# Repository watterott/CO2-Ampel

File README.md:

# CO2-Ampel
The CO2-Ampel is a traffic light to show the carbon dioxide concentration in a room.

* [Microchip ATSAMD21](https://www.microchip.com/wwwproducts/en/ATSAMD21G18) ARM Cortex-M0+ Microcontroller
* Sensirion [SCD30](https://www.sensirion.com/en/environmental-sensors/carbon-dioxide-sensors/carbon-dioxide-sensors-scd30/) or [SCD40/SCD41](https://www.sensirion.com/en/environmental-sensors/carbon-dioxide-sensors/carbon-dioxide-sensor-scd4x/) CO2 Sensor
* Intelligent WS2812 RGB-LEDs
* Acoustic Buzzer
* Plus Version:
  * [Microchip ATWINC1500B](http://www.microchip.com/wwwproducts/en/ATWINC1500) WiFi/WLAN Network Controller
* Pro Version:
  * Air Pressure Sensor
  * [Microchip ATWINC1500B](http://www.microchip.com/wwwproducts/en/ATWINC1500) WiFi/WLAN Network Controller (optional)
  * [HopeRF RFM95W/RFM96W](https://www.hoperf.com/modules/lora/index.html) LoRa Transceiver (optional)
* USB-C connector for power and data/programming
* USB CDC+MSC Bootloader (Arduino compatible)
* Open-Source and released under the [Creative Commons Attribution Share-Alike License](https://creativecommons.org/licenses/by-sa/4.0/).
* **[Documentation on learn.watterott.com](https://learn.watterott.com/breakouts/co2-ampel/)**

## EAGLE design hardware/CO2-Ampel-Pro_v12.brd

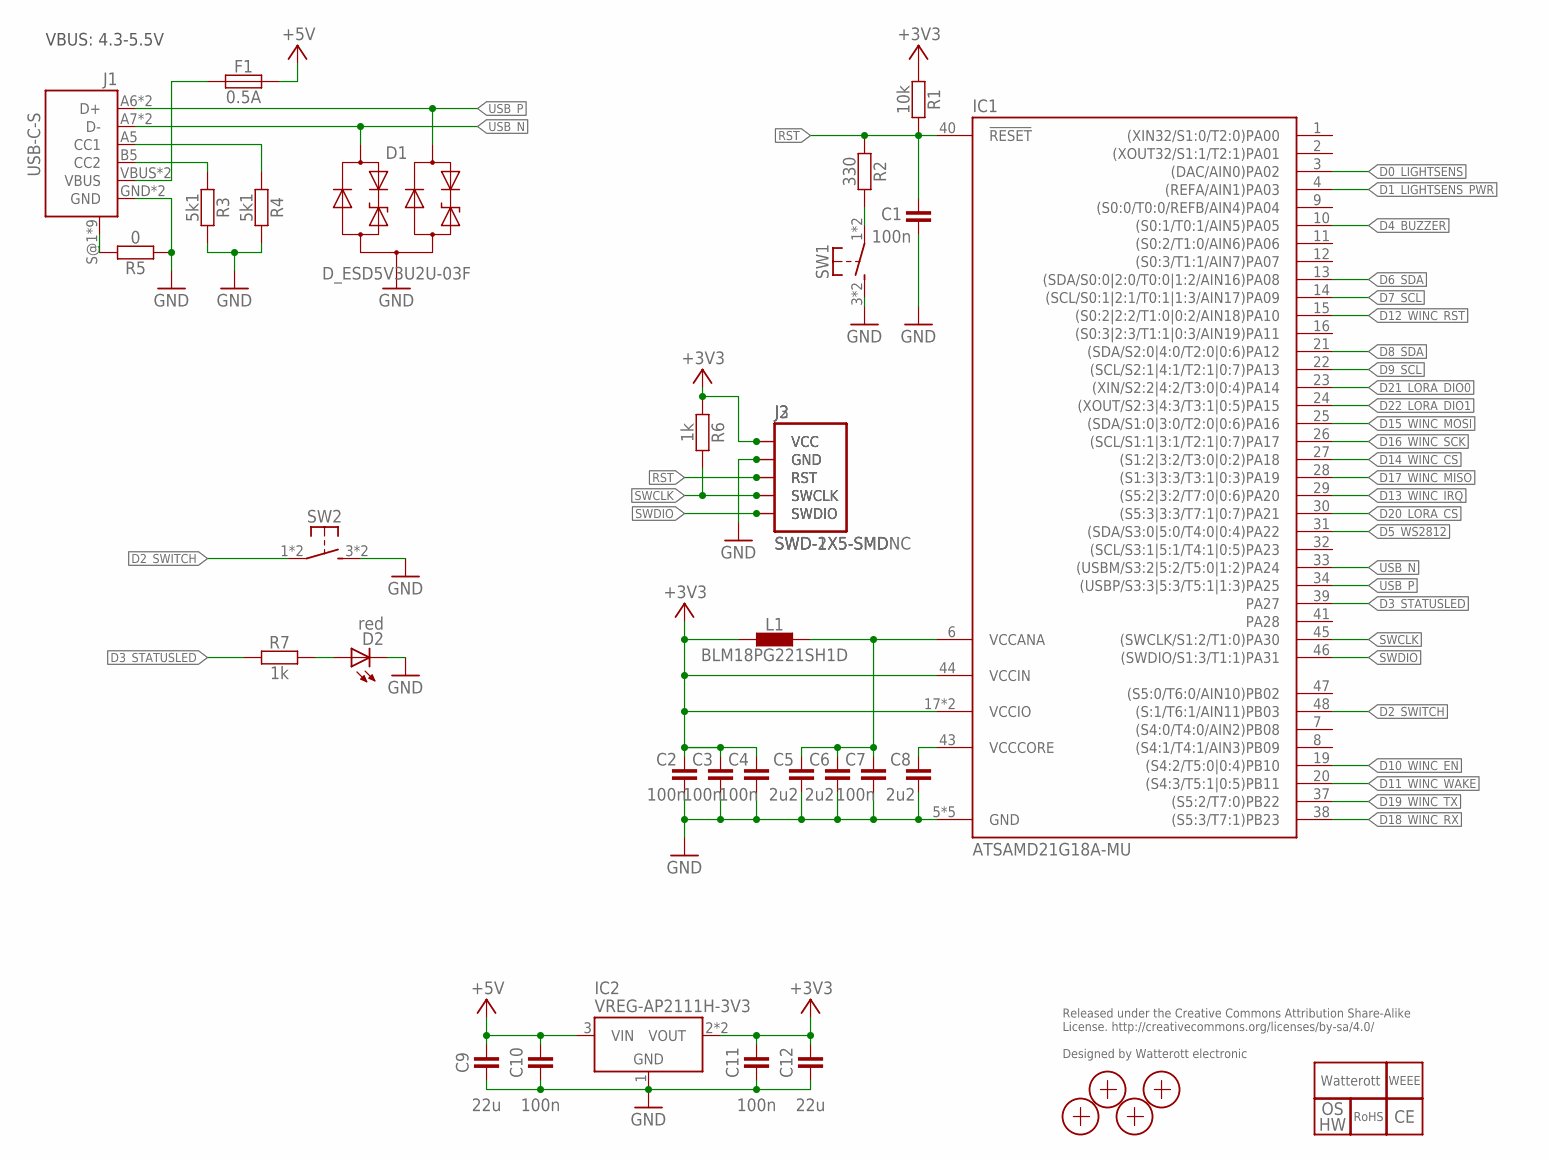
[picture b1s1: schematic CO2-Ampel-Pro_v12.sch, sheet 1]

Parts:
C1, C2, C3, C4, C7, C10, C11: 100n; C0402
C5, C6, C8: 2u2; C0402
C9, C12: 22u; C0805
D1: D_ESD5V3U2U-03F; SOT723
D2: red; C0603
F1: 0.5A; C0805
IC1: ATSAMD21G18A-MU; QFN48-PAD
IC2: VREG-AP2111H-3V3; SOT223
J1: USB-C-S
J2: SWD-2X5-SMD; SWD-2X5_SMD
J3: SWD-1X5-SMDNC; SWD-1X5_SMDNC
L1: BLM18PG221SH1D; C0603
LOGO1: LOGO_SPARK-4; SPARK_4MM
LOGO2: LOGO_WEEE-4; WEEE_4MM
LOGO3: OSHW_LOGOX0070; OSHW_3MM
LOGO4: LOGO_ROHS-4; ROHS_4MM
LOGO5: LOGO_CE-4; CE_4MM
R1: 10k; C0402
R2: 330; C0402
R3, R4: 5k1; C0402
R5: 0; C0603
R6, R7: 1k; C0402
SW1: PTS645SK50SMTR92-Red; PTS840P
SW2: PTS645SH50SMTR92-Grey; PTS840P
X1, X2, X3, X4: PASSER-07; PASSER_07MM

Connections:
+3V3: C2.2, C3.2, C4.2, C11.2, C12.2, IC1.17 (VCCIO), IC1.36 (VCCIO), IC1.44 (VCCIN), IC2.2 (VOUT), IC2.4 (VOUT), J2.VCC, J3.1-VCC (VCC), L1.1, R1.1, R6.1; also elsewhere on the board
+5V: C9.2, C10.2, F1.2, IC2.3 (VIN); also elsewhere on the board
CC1: J1.A5 (CC1), R4.1
CC2: J1.B5 (CC2), R3.1
D0_LIGHTSENS: IC1.3 ((DAC/AIN0)PA02); also elsewhere on the board
D1_LIGHTSENS_PWR: IC1.4 ((REFA/AIN1)PA03); also elsewhere on the board
D2_SWITCH: IC1.48 ((S:1/T6:1/AIN11)PB03), SW2.1, SW2.2 (P1)
D3_STATUSLED: IC1.39 (PA27), R7.1
D4_BUZZER: IC1.10 ((S0:1/T0:1/AIN5)PA05); also elsewhere on the board
D5_WS2812: IC1.31 ((SDA/S3:0|5:0/T4:0|0:4)PA22); also elsewhere on the board
D6_SDA: IC1.13 ((SDA/S0:0|2:0/T0:0|1:2/AIN16)PA08); also elsewhere on the board
D7_SCL: IC1.14 ((SCL/S0:1|2:1/T0:1|1:3/AIN17)PA09); also elsewhere on the board
D8_SDA: IC1.21 ((SDA/S2:0|4:0/T2:0|0:6)PA12); also elsewhere on the board
D9_SCL: IC1.22 ((SCL/S2:1|4:1/T2:1|0:7)PA13); also elsewhere on the board
D10_WINC_EN: IC1.19 ((S4:2/T5:0|0:4)PB10); also elsewhere on the board
D11_WINC_WAKE: IC1.20 ((S4:3/T5:1|0:5)PB11); also elsewhere on the board
D12_WINC_RST: IC1.15 ((S0:2|2:2/T1:0|0:2/AIN18)PA10); also elsewhere on the board
D13_WINC_IRQ: IC1.29 ((S5:2|3:2/T7:0|0:6)PA20); also elsewhere on the board
D14_WINC_CS: IC1.27 ((S1:2|3:2/T3:0|0:2)PA18); also elsewhere on the board
D15_WINC_MOSI: IC1.25 ((SDA/S1:0|3:0/T2:0|0:6)PA16); also elsewhere on the board
D16_WINC_SCK: IC1.26 ((SCL/S1:1|3:1/T2:1|0:7)PA17); also elsewhere on the board
D17_WINC_MISO: IC1.28 ((S1:3|3:3/T3:1|0:3)PA19); also elsewhere on the board
D18_WINC_RX: IC1.38 ((S5:3/T7:1)PB23); also elsewhere on the board
D19_WINC_TX: IC1.37 ((S5:2/T7:0)PB22); also elsewhere on the board
D20_LORA_CS: IC1.30 ((S5:3|3:3/T7:1|0:7)PA21); also elsewhere on the board
D21_LORA_DIO0: IC1.23 ((XIN/S2:2|4:2/T3:0|0:4)PA14); also elsewhere on the board
D22_LORA_DIO1: IC1.24 ((XOUT/S2:3|4:3/T3:1|0:5)PA15); also elsewhere on the board
GND: C1.1, C2.1, C3.1, C4.1, C5.1, C6.1, C7.1, C8.1, C9.1, C10.1, C11.1, C12.1, D1.3 (A), D2.C, IC1.5 (GND), IC1.18 (GND), IC1.35 (GND), IC1.42 (GND), IC1.TP (GND), IC2.1 (GND), J1.GND, J1.GND2 (GND), J2.GND@1 (GND), J2.GND@2 (GND), J2.GND@3 (GND), J3.2-GND (GND), R3.2, R4.2, R5.1, SW1.3 (S1), SW1.4 (S1), SW2.3 (S1), SW2.4 (S1); also elsewhere on the board
unnamed: D2.A, R7.2
unnamed: R2.2, SW1.1, SW1.2 (P1)
RST: C1.2, IC1.40 (!RESET), J2.RST, J3.3-RST (RST), R1.2, R2.1
SHLD: J1.S@1 (SHIELD), J1.S@2 (SHIELD), J1.S@3 (SHIELD), J1.S@4 (SHIELD), J1.S@5 (SHIELD), J1.S@6 (SHIELD), J1.S@7 (SHIELD), J1.S@8 (SHIELD), J1.S@9 (SHIELD), R5.2
SWCLK: IC1.45 ((SWCLK/S1:2/T1:0)PA30), J2.SWCLK, J3.4-SWDCLK (SWCLK), R6.2
SWDIO: IC1.46 ((SWDIO/S1:3/T1:1)PA31), J2.SWDIO, J3.5-SWDIO (SWDIO)
USB_N: D1.1 (C1), IC1.33 ((USBM/S3:2|5:2/T5:0|1:2)PA24), J1.A7 (D-), J1.B7 (D-)
USB_P: D1.2 (C2), IC1.34 ((USBP/S3:3|5:3/T5:1|1:3)PA25), J1.A6 (D+), J1.B6 (D+)
VBUS: F1.1, J1.VBUS, J1.VBUS2 (VBUS)
VCCANA: C5.2, C6.2, C7.2, IC1.6 (VCCANA), L1.2
VCCCORE: C8.2, IC1.43 (VCCCORE)

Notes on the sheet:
Released under the Creative Commons Attribution Share-Alike License. http://creativecommons.org/licenses/by-sa/4.0/ Designed by Watterott electronic
VBUS: 4.3-5.5V

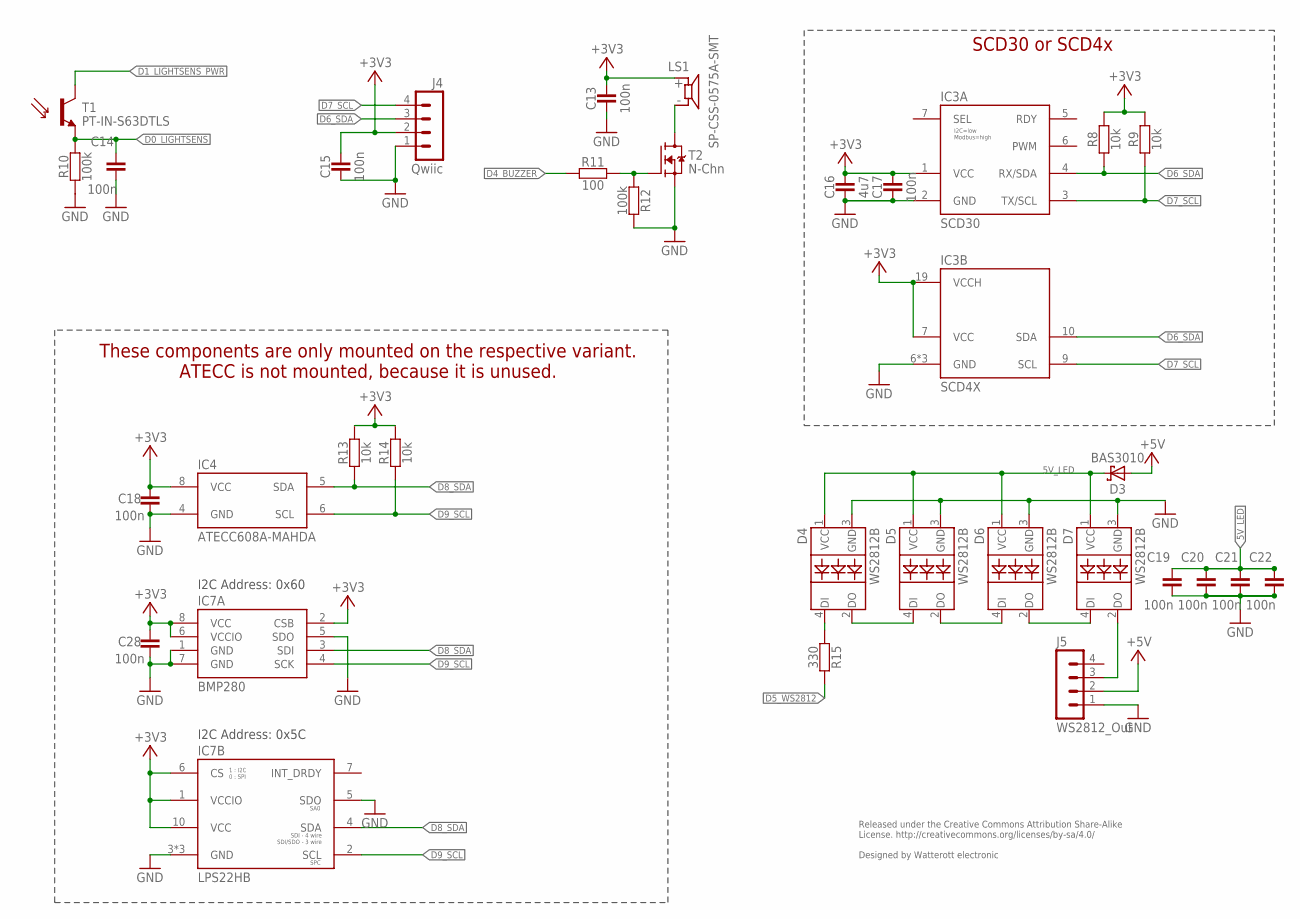
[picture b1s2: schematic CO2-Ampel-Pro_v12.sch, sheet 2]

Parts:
C13, C14, C15, C17, C18, C19, C20, C21, C22, C28: 100n; C0402
C16: 4u7; C0402
D3: BAS3010; SOD323
D4, D5, D6, D7: WS2812B
IC3A: SCD30
IC3B: SCD4X
IC4: ATECC608A-MAHDA; UDFN8
IC7A: BMP280; LGA8
IC7B: LPS22HB
J4: Qwiic; JST_SM04B-SRSS-TB
J5: WS2812_Out; JST_SM04B-SRSS-TB
LS1: SP-CSS-0575A-SMT; CUI_CSS-0575A-SMT
R8, R9, R13, R14: 10k; C0402
R10, R12: 100k; C0402
R11: 100; C0402
R15: 330; C0402
T1: PT-IN-S63DTLS; C0603T
T2: N-Chn; SOT23

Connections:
5V_LED: C19.2, C20.2, C21.2, C22.2, D3.C, D4.1 (VCC), D5.1 (VCC), D6.1 (VCC), D7.1 (VCC)
+3V3: C13.2, C15.2, C16.2, C17.2, C18.2, C28.2, IC3A.1 (VCC), IC3B.7 (VCC), IC3B.19 (VCCH), IC4.8 (VCC), IC7A.2 (CSB), IC7A.6 (VCCIO), IC7A.8 (VCC), IC7B.1 (VCCIO), IC7B.6 (CS), IC7B.10 (VCC), J4.2, LS1.+, R8.2, R9.2, R13.2, R14.2; also elsewhere on the board
+5V: D3.A, J5.2; also elsewhere on the board
D0_LIGHTSENS: C14.2, R10.2, T1.E; also elsewhere on the board
D1_LIGHTSENS_PWR: T1.C; also elsewhere on the board
D4_BUZZER: R11.1; also elsewhere on the board
D5_WS2812: R15.2; also elsewhere on the board
D6_SDA: IC3A.4 (RX/SDA), IC3B.10 (SDA), J4.3, R8.1; also elsewhere on the board
D7_SCL: IC3A.3 (TX/SCL), IC3B.9 (SCL), J4.4, R9.1; also elsewhere on the board
D8_SDA: IC4.5 (SDA), IC7A.3 (SDI), IC7B.4 (SDA), R13.1; also elsewhere on the board
D9_SCL: IC4.6 (SCL), IC7A.4 (SCK), IC7B.2 (SCL), R14.1; also elsewhere on the board
GND: C13.1, C14.1, C15.1, C16.1, C17.1, C18.1, C19.1, C20.1, C21.1, C22.1, C28.1, D4.3 (GND), D5.3 (GND), D6.3 (GND), D7.3 (GND), IC3A.2 (GND), IC3B.6 (GND), IC3B.20 (GND), IC3B.21 (GND), IC4.4 (GND), IC7A.1 (GND), IC7A.5 (SDO), IC7A.7 (GND), IC7B.3 (GND), IC7B.5 (SDO), IC7B.8 (GND), IC7B.9 (GND), J4.1, J5.1, R10.1, R12.2, T2.2 (S); also elsewhere on the board
unnamed: LS1.- (N), T2.3 (D)
unnamed: R11.2, R12.1, T2.1 (G)
W1IN: D4.4 (DI), R15.1
W1OUT: D4.2 (DO), D5.4 (DI)
W2OUT: D5.2 (DO), D6.4 (DI)
W3OUT: D6.2 (DO), D7.4 (DI)
W4OUT: D7.2 (DO), J5.3

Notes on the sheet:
I2C Address: 0x60
Released under the Creative Commons Attribution Share-Alike License. http://creativecommons.org/licenses/by-sa/4.0/ Designed by Watterott electronic
I2C Address: 0x5C
These components are only mounted on the respective variant. ATECC is not mounted, because it is unused.
SCD30 or SCD4x

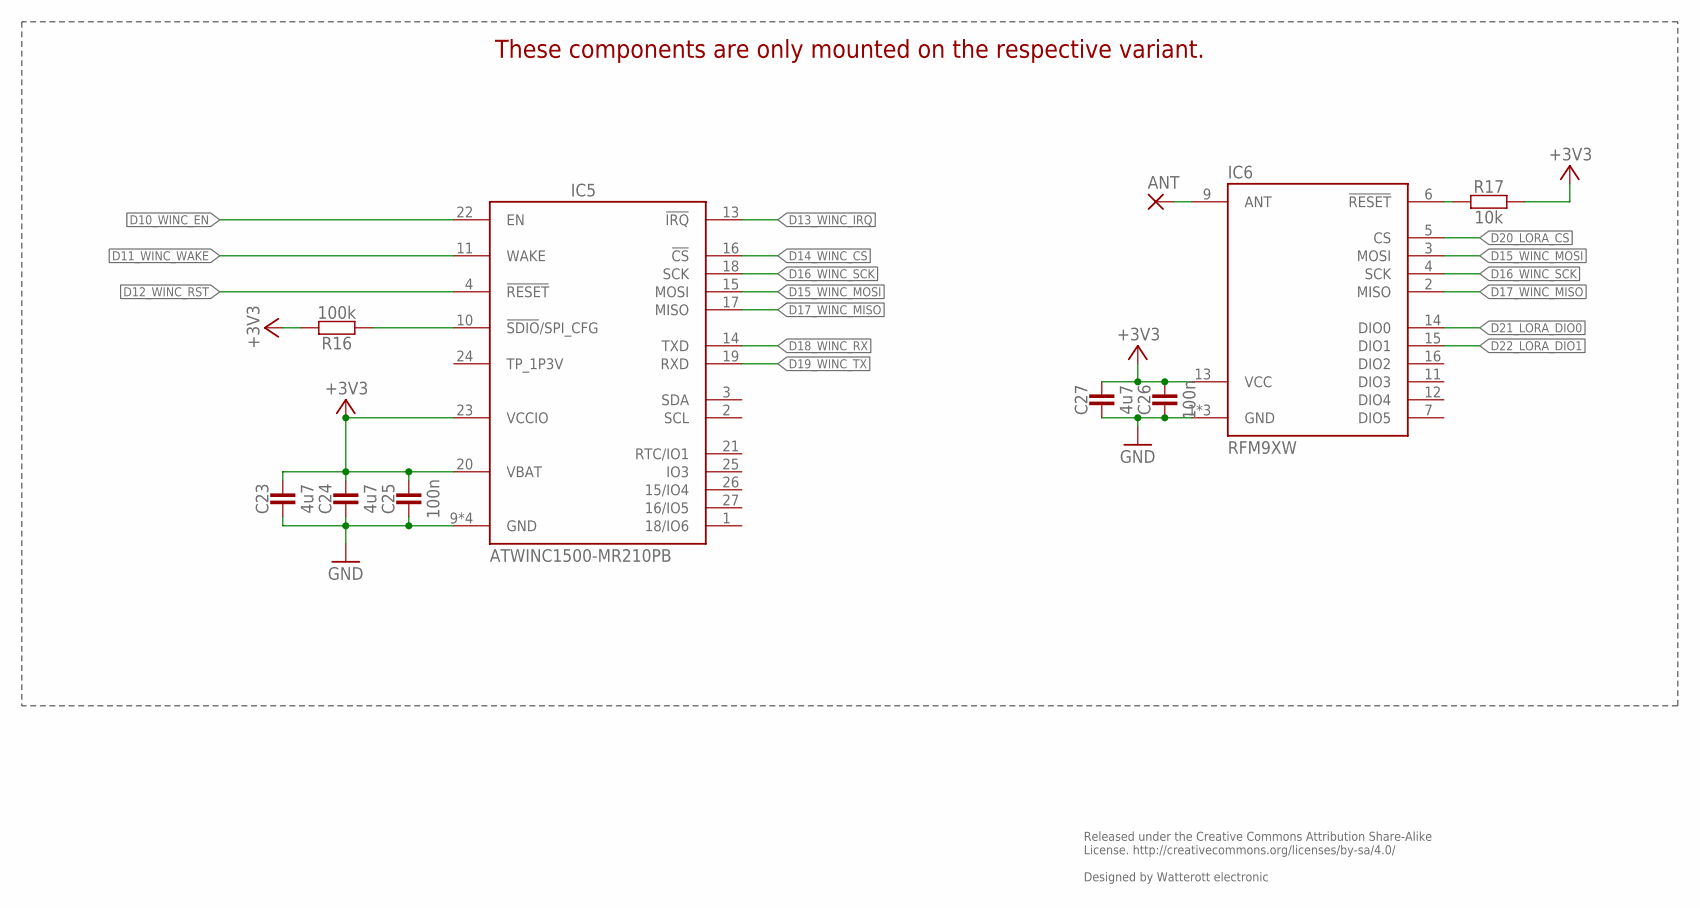
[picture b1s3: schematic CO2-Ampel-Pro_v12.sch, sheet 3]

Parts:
ANT: 1,6/0,9
C23, C24, C27: 4u7; C0402
C25, C26: 100n; C0402
IC5: ATWINC1500-MR210PB; ATWINC1500-MX210
IC6: RFM9XW; RFM9X
R16: 100k; C0402
R17: 10k; C0402

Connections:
+3V3: C23.2, C24.2, C25.2, C26.2, C27.2, IC5.20 (VBAT), IC5.23 (VCCIO), IC6.13 (VCC), R16.2, R17.2; also elsewhere on the board
CFG: IC5.10 (!SDIO!/SPI_CFG), R16.1
D10_WINC_EN: IC5.22 (EN); also elsewhere on the board
D11_WINC_WAKE: IC5.11 (WAKE); also elsewhere on the board
D12_WINC_RST: IC5.4 (!RESET); also elsewhere on the board
D13_WINC_IRQ: IC5.13 (!IRQ); also elsewhere on the board
D14_WINC_CS: IC5.16 (!CS); also elsewhere on the board
D15_WINC_MOSI: IC5.15 (MOSI), IC6.3 (MOSI); also elsewhere on the board
D16_WINC_SCK: IC5.18 (SCK), IC6.4 (SCK); also elsewhere on the board
D17_WINC_MISO: IC5.17 (MISO), IC6.2 (MISO); also elsewhere on the board
D18_WINC_RX: IC5.14 (TXD); also elsewhere on the board
D19_WINC_TX: IC5.19 (RXD); also elsewhere on the board
D20_LORA_CS: IC6.5 (CS); also elsewhere on the board
D21_LORA_DIO0: IC6.14 (DIO0); also elsewhere on the board
D22_LORA_DIO1: IC6.15 (DIO1); also elsewhere on the board
GND: C23.1, C24.1, C25.1, C26.1, C27.1, IC5.9 (GND), IC5.12 (GND), IC5.28 (GND), IC5.GND, IC6.1 (GND), IC6.8 (GND), IC6.10 (GND); also elsewhere on the board
unnamed: ANT.1, IC6.9 (ANT)
unnamed: IC6.6 (!RESET), R17.1

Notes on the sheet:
Released under the Creative Commons Attribution Share-Alike License. http://creativecommons.org/licenses/by-sa/4.0/ Designed by Watterott electronic
These components are only mounted on the respective variant.

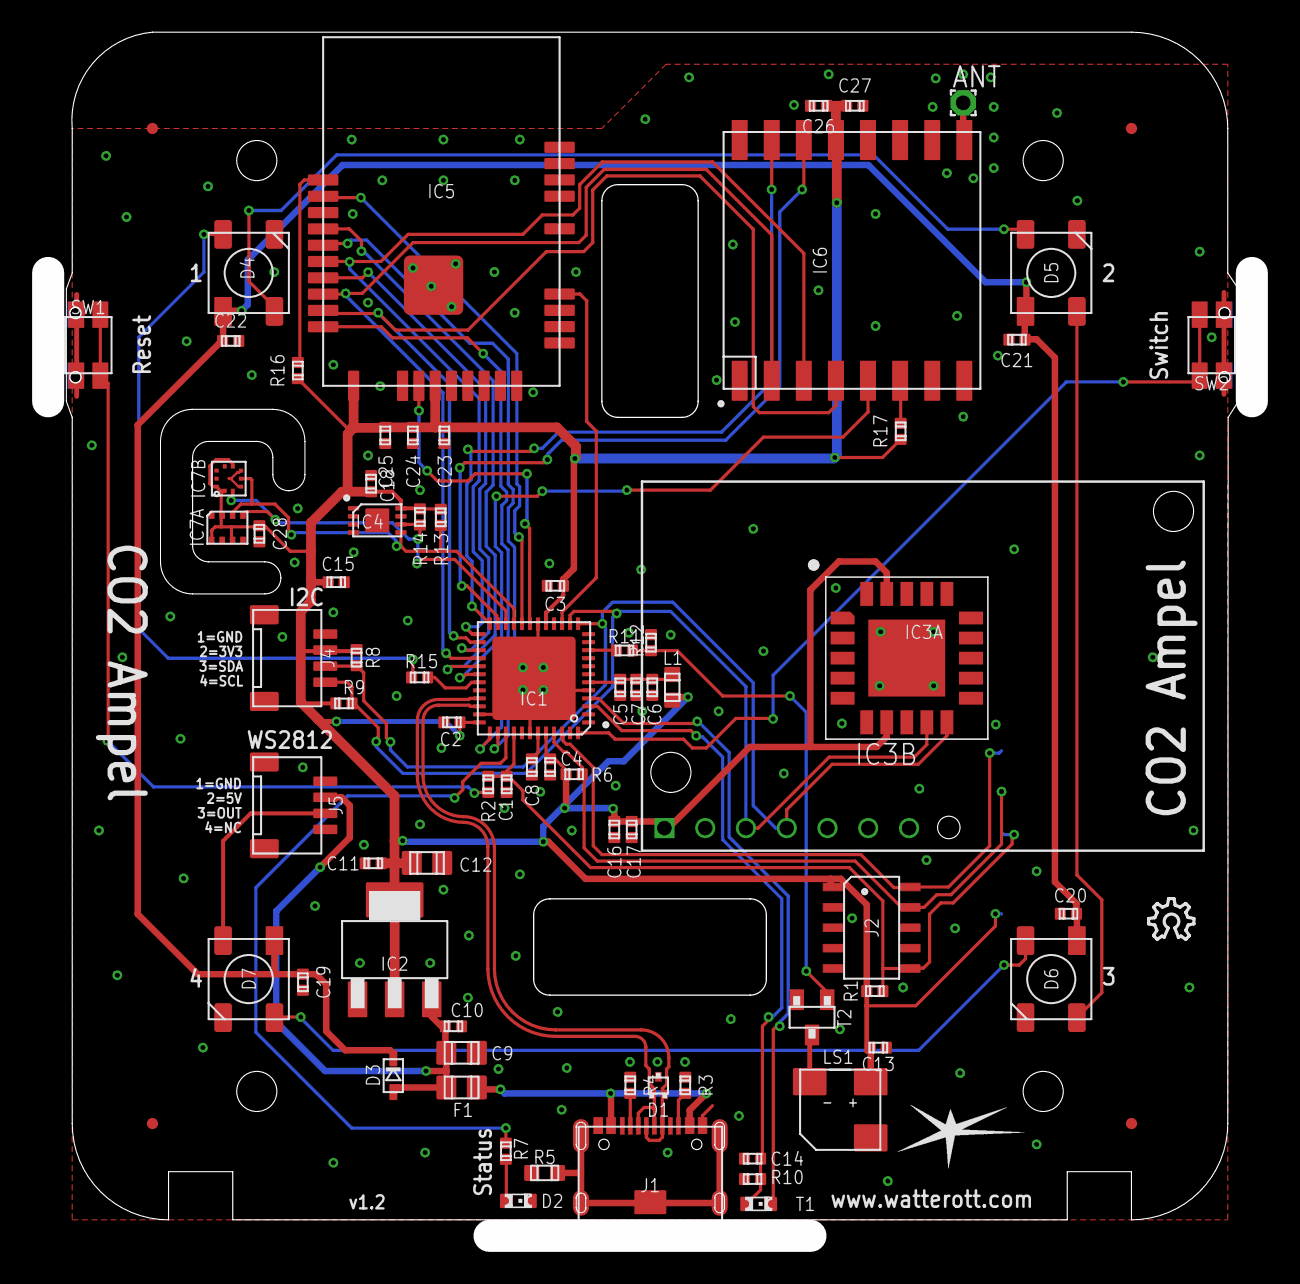
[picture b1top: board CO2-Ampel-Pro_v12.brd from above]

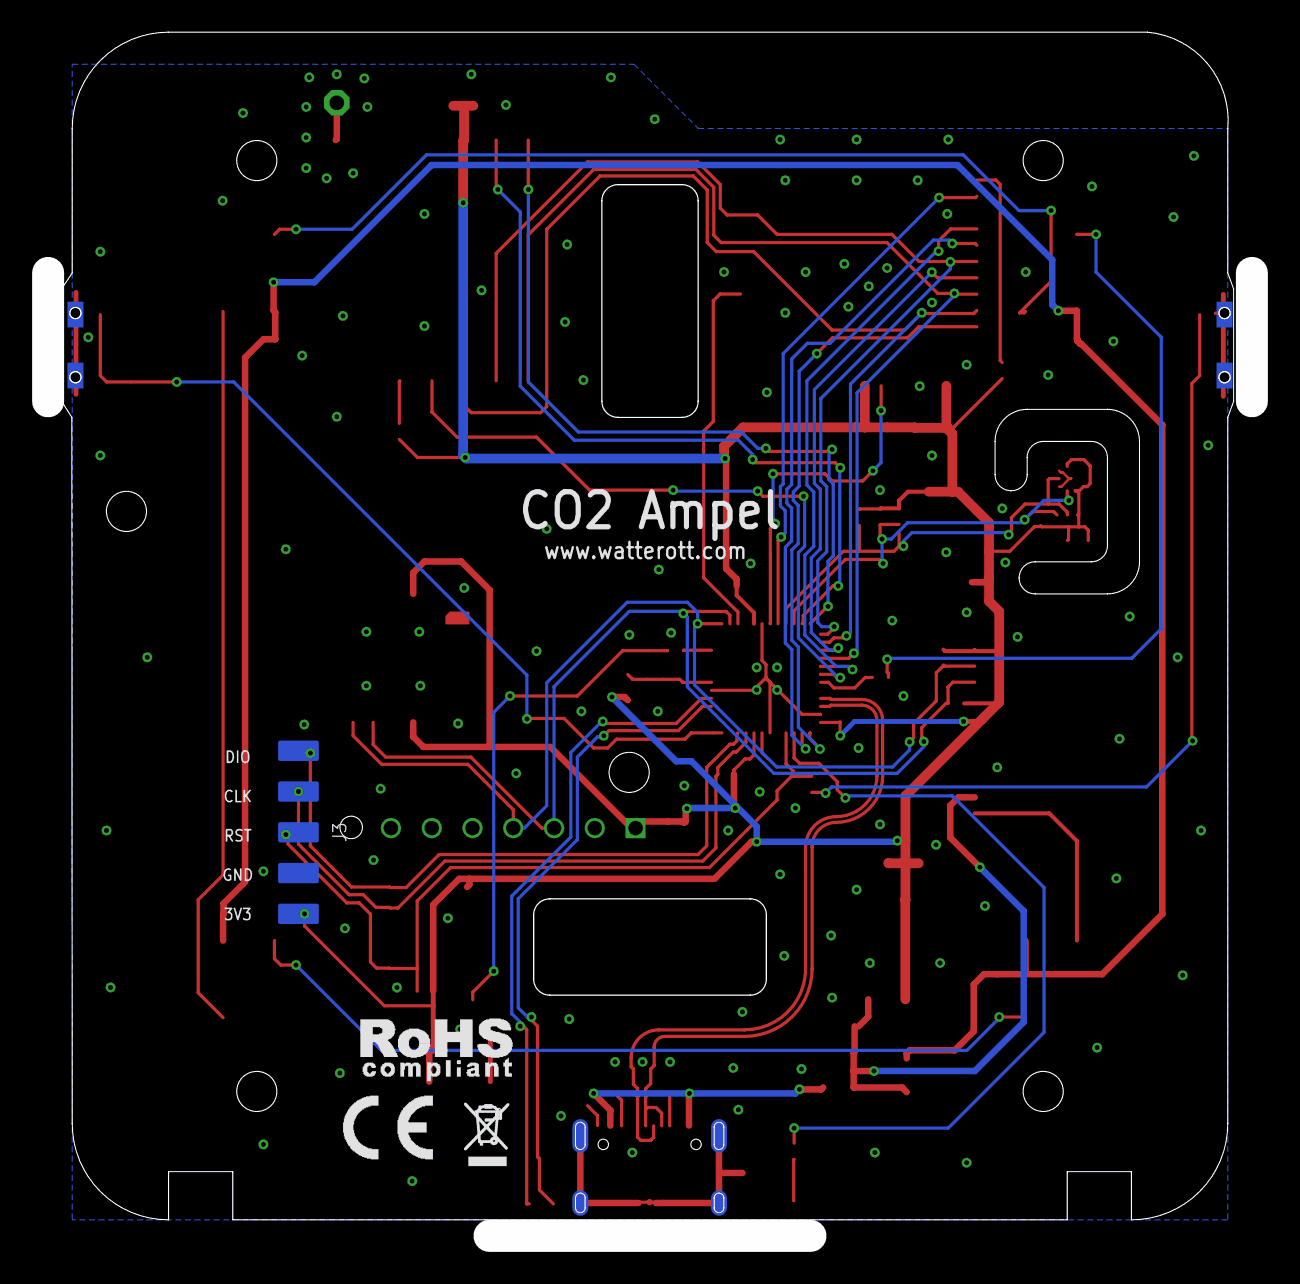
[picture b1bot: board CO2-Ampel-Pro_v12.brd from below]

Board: 2 copper layers, 75.0 x 74.0 mm, 83 parts (4 on the bottom side), 50 nets.

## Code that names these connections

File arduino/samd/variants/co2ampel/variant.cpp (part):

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 |            |                  |        |                 |   EIC  | ADC |  AC | PTC | DAC | SERCOMx | SERCOMx |  TCCx  |  TCCx  |    COM   | AC/GLCK  |
 |            |                  |        |                 |(EXTINT)|(AIN)|(AIN)|     |     | (x/PAD) | (x/PAD) | (x/WO) | (x/WO) |          |          |
 +------------+------------------+--------+-----------------+--------+-----+-----+-----+-----+---------+---------+--------+--------+----------+----------+
 | 00         | Light Sensor     |  PA02  |                 |   02   | *00 |     | Y00 | OUT |         |         |        |        |          |          |
 | 01         | Light Sensor Pwr |  PA03  |                 |   03   |  01 |     | Y01 |     |         |         |        |        |          |          |
 | 02         | Switch           |  PB03  |                 |  *03   | *11 |     | Y09 |     |         |   5/01  |        |        |          |          |
 | 03         | LED red          |  PA27  |                 |   15   |     |     |     |     |         |         |        |        |          | GCLK_IO0 |
 | 04         | Buzzer           |  PA05  |                 |   05   | *05 |  01 | Y03 |     |         |   0/01  |*TCC0/1 |        |          |          |
 | 05         | WS2812 LEDs      |  PA22  |                 |  *06   |     |     | X10 |     |   3/00  |   5/00  |* TC4/0 | TCC0/4 |          | GCLK_IO6 |
 +------------+------------------+--------+-----------------+--------------------+-----+-----+---------+---------+--------+--------+----------+----------+
 | 06         | SDA SCD30        |  PA08  |                 |   NMI  | *16 |     | X00 |     |  *0/00  |   2/00  | TCC0/0 | TCC1/2 | I2S/SD1  |          |
 | 07         | SCL SCD30        |  PA09  |                 |   09   | *17 |     | X01 |     |  *0/01  |   2/01  | TCC0/1 | TCC1/3 | I2S/MCK0 |          |
 +------------+------------------+--------+-----------------+--------------------+-----+-----+---------+---------+--------+--------+----------+----------+
 | 08         | SDA ATECC        |  PA12  |                 |   12   |     |     |     |     |  *2/00  |   4/00  | TCC2/0 | TCC0/6 |          | AC/CMP0  |
 | 09         | SCL ATECC        |  PA13  |                 |   13   |     |     |     |     |  *2/01  |   4/01  | TCC2/1 | TCC0/7 |          | AC/CMP1  |
  +------------+------------------+--------+-----------------+--------------------+-----+-----+---------+---------+--------+--------+----------+----------+
 | 10         | WINC En          |  PB10  |                 |  *10   |     |     |     |     |         |   4/02  |* TC5/0 | TCC0/4 | I2S/MCK1 | GCLK_IO4 |
 | 11         | WINC Wake        |  PB11  |                 |  *11   |     |     |     |     |         |   4/03  |* TC5/1 | TCC0/5 | I2S/SCK1 | GCLK_IO5 |
 | 12         | WINC Rst         |  PA10  |                 |   10   | *18 |     | X02 |     |   0/02  |   2/02  |*TCC1/0 | TCC0/2 | I2S/SCK0 | GCLK_IO4 |
 | 13         | WINC Irq         |  PA20  |                 |  *04   |     |     | X08 |     |   5/02  |   3/02  |        |*TCC0/6 | I2S/SCK0 | GCLK_IO4 |
 | 14         | WINC CS          |  PA18  |                 |   02   |     |     | X06 |     |   1/02  |   3/02  |  TC3/0 | TCC0/2 |          | AC/CMP0  |
 | 15         | WINC MOSI        |  PA16  |                 |  *00   |     |     | X04 |     |  *1/00  |   3/00  |*TCC2/0 | TCC0/6 |          | GCLK_IO2 |
 | 16         | WINC SCK         |  PA17  |                 |  *01   |     |     | X05 |     |  *1/01  |   3/01  | TCC2/1 | TCC0/7 |          | GCLK_IO3 |
 | 17         | WINC MISO        |  PA19  |                 |   03   |     |     | X07 |     |  *1/03  |   3/03  |* TC3/1 | TCC0/3 | I2S/SD0  | AC/CMP1  |
 | 18         | WINC RX          |  PB23  |                 |   07   |     |     |     |     |         |  *5/03  |        |        |          | GCLK_IO1 |
 | 19         | WINC TX          |  PB22  |                 |   06   |     |     |     |     |         |  *5/02  |        |        |          | GCLK_IO0 |
 | 20         | RFM9X CS         |  PA21  |                 |  *05   |     |     | X09 |     |   5/03  |   3/03  |        |*TCC0/7 | I2S/FS0  | GCLK_IO5 |
 | 21         | RFM9X DIO0       |  PA14  |                 |   14   |     |     |     |     |   2/02  |   4/02  |  TC3/0 | TCC0/4 |          | GCLK_IO0 |
 | 22         | RFM9X DIO1       |  PA15  |                 |   15   |     |     |     |     |  *2/03  |   4/03  |  TC3/1 | TCC0/5 |          | GCLK_IO1 |
 +------------+------------------+--------+-----------------+--------+-----+-----+-----+-----+---------+---------+--------+--------+----------+----------+
 */
  { PORTA,  2, PIO_ANALOG,  (PIN_ATTR_DIGITAL|PIN_ATTR_ANALOG /*DAC*/        ), ADC_Channel0,   NOT_ON_PWM, NOT_ON_TIMER, EXTERNAL_INT_2    }, // Light
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 |            |                  |        |                 |(EXTINT)|(AIN)|(AIN)|     |     | (x/PAD) | (x/PAD) | (x/WO) | (x/WO) |          |          |
 +------------+------------------+--------+-----------------+--------+-----+-----+-----+-----+---------+---------+--------+--------+----------+----------+
 |            |       USB        |        |                 |        |     |     |     |     |         |         |        |        |          |          |
 | 23         |                  |  PA24  | USB N           |   12   |     |     |     |     |   3/02  |   5/02  |  TC5/0 | TCC1/2 | USB/DM   |          |
 | 24         |                  |  PA25  | USB P           |   13   |     |     |     |     |   3/03  |   5/03  |  TC5/1 | TCC1/3 | USB/DP   |          |
 +------------+------------------+--------+-----------------+--------+-----+-----+-----+-----+---------+---------+--------+--------+----------+----------+
 |            | 32768Hz Crystal  |        |                 |        |     |     |     |     |         |         |        |        |          |          |
 | 25         |                  |  PA00  | XIN32           |   00   |     |     |     |     |         |   1/00  | TCC2/0 |        |          |          |
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  PORT->Group[0].OUTSET.reg = PORT_PA21; // high

  // I2C pins
  PORT->Group[0].PINCFG[PIN_PA08].reg |= PORT_PINCFG_PULLEN; // PA08 SDA1
  PORT->Group[0].OUTSET.reg = PORT_PA08; // pull-up

  PORT->Group[0].PINCFG[PIN_PA09].reg |= PORT_PINCFG_PULLEN; // PA09 SDA1
  PORT->Group[0].OUTSET.reg = PORT_PA09; // pull-up

  PORT->Group[0].PINCFG[PIN_PA12].reg |= PORT_PINCFG_PULLEN; // PA12 SDA2
  PORT->Group[0].OUTSET.reg = PORT_PA12; // pull-up

  PORT->Group[0].PINCFG[PIN_PA13].reg |= PORT_PINCFG_PULLEN; // PA13 SDA2
  PORT->Group[0].OUTSET.reg = PORT_PA13; // pull-up
}

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
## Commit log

2020-10-31 added readme and schematics
2020-10-31 Arduino BSP
2020-10-31 rename file
2020-11-04 update BSP
2020-11-12 added layout and schematics
2020-12-02 updated schematics
2020-12-02 added rev 1.1
2020-12-15 update libs
2020-12-23 add getAltitudeCompensation()
2021-01-06 Color with linear hue mapping
2021-01-07 Längerer rot Bereich
2021-01-07 Change readme
2021-01-07 Hue from green to red with green below 300ppm
2021-01-07 Gitignore
2021-01-07 some comments
2021-01-07 Bugfix for colormapping now we map from light blue to red
2021-01-08 update lib
2021-01-08 initVariant() fix
2021-01-08 Better hue scale more green range
2021-01-13 fix warning
2021-01-29 enable pullups on I2C
2021-02-01 update pins for LoRa module
2021-02-01 updated libs
2021-02-01 added examples
2021-03-02 Fix docs URL
    More direct link right to the product's page
2021-03-03 Update issue templates
2021-04-22 set measurement interval to 2s
    Thanks to @ernstkl
2021-04-22 WiFi SSID and key up to 64 characters
2021-05-09 SCD4x support
2021-05-27 SCD30/SCD4x air pressure compensation
2021-06-04 WINC1500 detection changed
2021-06-07 Buzzer start delay
2021-06-08 Temperature offset for pro variant
2021-08-18 added CO2-Ampel Pro v1.2
2021-08-18 added enclosure
2021-11-29 Set checksum for latest version
2022-01-20 SCD4x bugfixes
2022-01-22 configure buzzer threshold via web interface
2022-02-07 static IP settings
2022-02-19 JSON endpoint
2022-02-20 webinterface
2022-02-20 website 2min auto-refresh
2022-02-21 add REST URL for Checkmk minimal agent
2022-03-05 clean-up
2022-03-22 receive timeout
2022-03-22 no favicon
2022-03-30 receive timeout increased
2022-04-18 check whether connecting attempt was successful in wifi_start
2023-07-01 Several improvements for Checkmk endpoint: - add firmware version to both JSON and CMK endpoint (detect upgradable devices) - add section on network to help identify devices in routed networks - add 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

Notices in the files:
arduino/samd/variants/co2ampel/variant.cpp:
Copyright (c) 2014-2015 Arduino LLC.  All right reserved.
